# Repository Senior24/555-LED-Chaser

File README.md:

# 555 LED Chaser

I designed Led chaser in diamond-shaped pcb (to give superman look). I accomplished this by following a guide. I tried to avoid via's in pcb and I did it

Gerbers and BOM are in the production folder

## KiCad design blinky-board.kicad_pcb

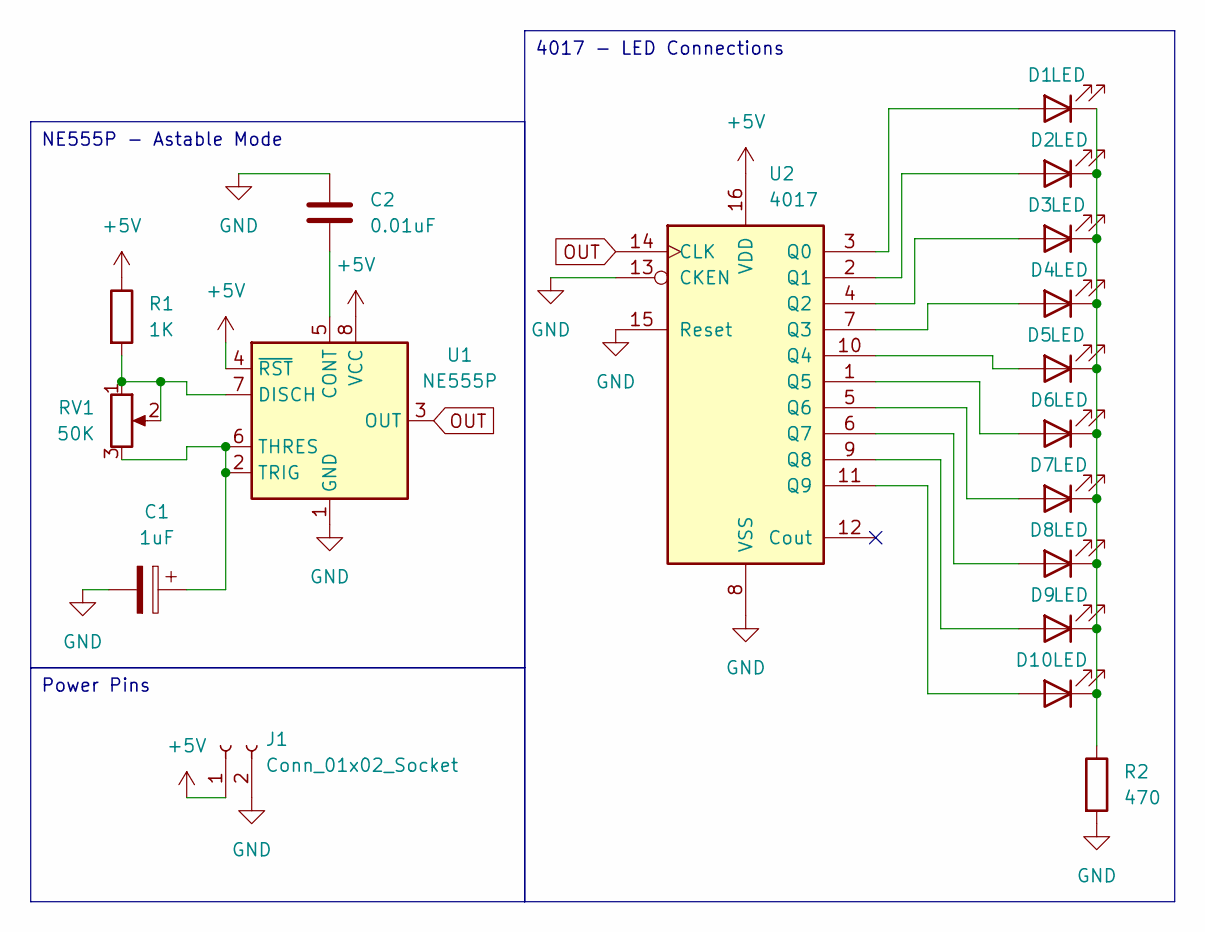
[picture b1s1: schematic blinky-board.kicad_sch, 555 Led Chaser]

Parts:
C1: 1uF; CP_Radial_D5.0mm_P2.00mm
C2: 0.01uF; C_Disc_D7.5mm_W2.5mm_P5.00mm
D1, D2, D3, D4, D5, D6, D7, D8, D9, D10: LED; LED_D3.0mm
J1: Conn_01x02_Socket; PinHeader_1x02_P2.54mm_Vertical
R1: 1K; R_Axial_DIN0207_L6.3mm_D2.5mm_P7.62mm_Horizontal
R2: 470; R_Axial_DIN0207_L6.3mm_D2.5mm_P7.62mm_Horizontal
RV1: 50K; Potentiometer_Vishay_T93YA_Vertical
U1: NE555P; DIP-8_W7.62mm
U2: 4017; N16

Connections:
+5V: J1.1, R1.1, U1.4 (~RST), U1.8 (VCC), U2.16 (VDD)
GND: C1.2, C2.1, J1.2, R2.2, U1.1 (GND), U2.8 (VSS), U2.13 (CKEN), U2.15 (Reset)
unnamed: D1.2 (A), U2.3 (Q0)
unnamed: D1.1 (K), D2.1 (K), D3.1 (K), D4.1 (K), D5.1 (K), D6.1 (K), D7.1 (K), D8.1 (K), D9.1 (K), D10.1 (K), R2.1
unnamed: D2.2 (A), U2.2 (Q1)
unnamed: D3.2 (A), U2.4 (Q2)
unnamed: D4.2 (A), U2.7 (Q3)
unnamed: D5.2 (A), U2.10 (Q4)
unnamed: D6.2 (A), U2.1 (Q5)
unnamed: D7.2 (A), U2.5 (Q6)
unnamed: D8.2 (A), U2.6 (Q7)
unnamed: D9.2 (A), U2.9 (Q8)
unnamed: D10.2 (A), U2.11 (Q9)
unnamed: C2.2, U1.5 (CONT)
unnamed: R1.2, RV1.1, RV1.2, U1.7 (DISCH)
unnamed: C1.1, RV1.3, U1.2 (TRIG), U1.6 (THRES)
OUT: U1.3 (OUT), U2.14 (CLK)

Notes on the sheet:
Power Pins
NE555P - Astable Mode
4017 - LED Connections

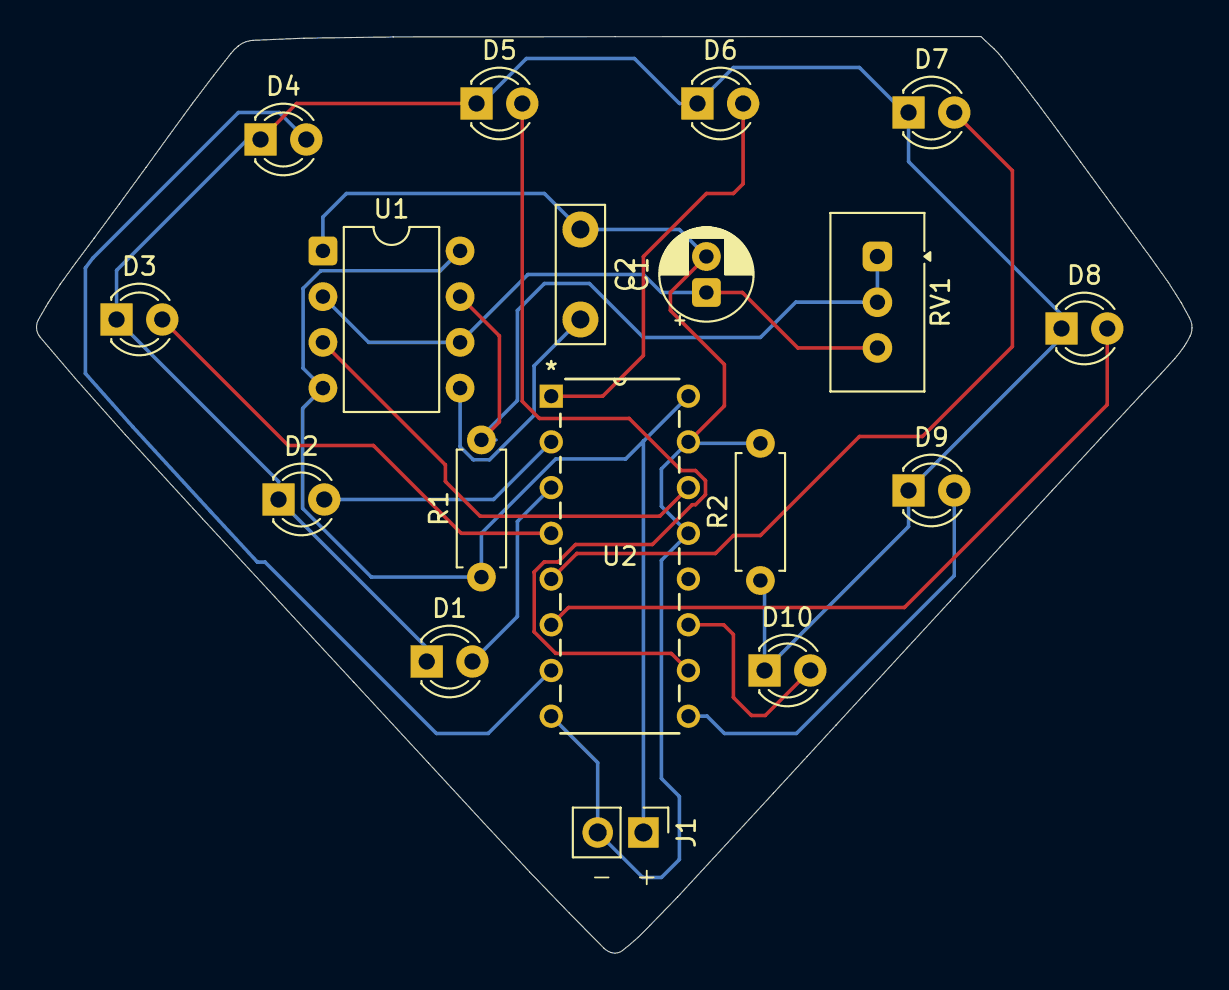
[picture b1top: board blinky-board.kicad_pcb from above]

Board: 2 copper layers, 64.2 x 50.9 mm, 18 parts (0 on the bottom side), 17 nets.

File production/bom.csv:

Designator,Footprint,Quantity,Value,LCSC Part #
C1,CP_Radial_D5.0mm_P2.00mm,1,1uF,
C2,C_Disc_D7.5mm_W2.5mm_P5.00mm,1,0.01uF,
"D1, D10, D2, D3, D4, D5, D6, D7, D8, D9",LED_D3.0mm,10,LED,
J1,PinHeader_1x02_P2.54mm_Vertical,1,Conn_01x02_Socket,
R1,R_Axial_DIN0207_L6.3mm_D2.5mm_P7.62mm_Horizontal,1,1K,
R2,R_Axial_DIN0207_L6.3mm_D2.5mm_P7.62mm_Horizontal,1,470,
RV1,Potentiometer_Vishay_T93YA_Vertical,1,50K,
U1,DIP-8_W7.62mm,1,NE555P,
U2,N16,1,4017,

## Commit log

2026-03-10 Uploaded files
2026-03-10 Update README.md
    Updated project title and added an image along with a description.
2026-03-13 Updated PCB F.Silkscreen
